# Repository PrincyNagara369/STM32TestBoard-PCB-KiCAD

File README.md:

# STM32TestBoard-PCB-KiCAD
Creating a PCB design for an STM32 test board using KiCad involves several steps. Below is a general outline of the process:

1. **Install KiCad:**
   If you haven't already, download and install the KiCad software from the official KiCad website (https://www.kicad-pcb.org/download/).

2. **Create a New Project:**
   - Open KiCad and create a new project for your STM32 test board.
   - Choose a suitable project name and location.

3. **Schematic Design:**
   - Start by creating a new schematic sheet in your project.
   - Add components to the schematic, including the STM32 microcontroller, power supply components, connectors, and any other peripherals you plan to include.
   - Connect the components by adding wires and creating appropriate nets.

4. **Component Libraries:**
   - Make sure you have the required component libraries for your components. KiCad comes with a set of default libraries, and you can also download additional libraries if needed.

5. **Footprint Assignment:**
   - Associate footprints with your schematic symbols. KiCad allows you to associate each component with a physical footprint used in the PCB layout.

6. **Schematic Annotation:**
   - Annotate the components on the schematic. KiCad will assign unique reference designators (e.g., U1, R1) to each component.

7. **Electrical Rule Check (ERC):**
   - Run an ERC to identify any potential connectivity or design rule errors in your schematic.

8. **Generate Netlist:**
   - Generate a netlist file from your schematic. The netlist is used to create the PCB layout.

9. **PCB Layout:**
   - Create a new PCB layout from the generated netlist.
   - Import footprints for your components or create custom footprints if necessary.
   - Place the components on the PCB layout, arranging them in a logical and organized manner.

10. **Connect Traces:**
    - Route the traces to connect the components according to your design.
    - Pay attention to signal integrity, power distribution, and ground plane.

11. **Design Rules Check (DRC):**
    - Run a DRC to ensure that your layout adheres to design rules such as minimum trace width, clearance, and other manufacturing specifications.

12. **Add Copper Pours and Planes:**
    - Create copper pours for power and ground connections.
    - Add ground and power planes if necessary for better signal integrity and noise reduction.

13. **3D Visualization:**
    - KiCad provides a 3D visualization tool that lets you preview your PCB in a realistic manner.

14. **Generate Gerber Files:**
    - Once you're satisfied with your PCB layout, generate the necessary Gerber files for manufacturing. These files include information about copper traces, solder mask, silkscreen, and more.

15. **Assembly Drawing:**
    - Create an assembly drawing that shows the component placements, reference designators, and other important details for assembling the PCB.

16. **Final Checks:**
    - Review your design thoroughly to ensure everything is correct and meets your requirements.

17. **Documentation:**
    - Create a documentation package that includes the schematic, PCB layout files, Gerber files, and any additional notes or instructions.

18. **Manufacturing:**
    - Send the Gerber files and other required documents to a PCB manufacturer for fabrication.

Remember that PCB design can be complex and requires attention to detail. It's also a good practice to consult the datasheets and reference manuals of your components, as well as any relevant PCB design guidelines from the microcontroller manufacturer. Additionally, there are many online resources, tutorials, and forums where you can find help and guidance during your KiCad PCB design journey.

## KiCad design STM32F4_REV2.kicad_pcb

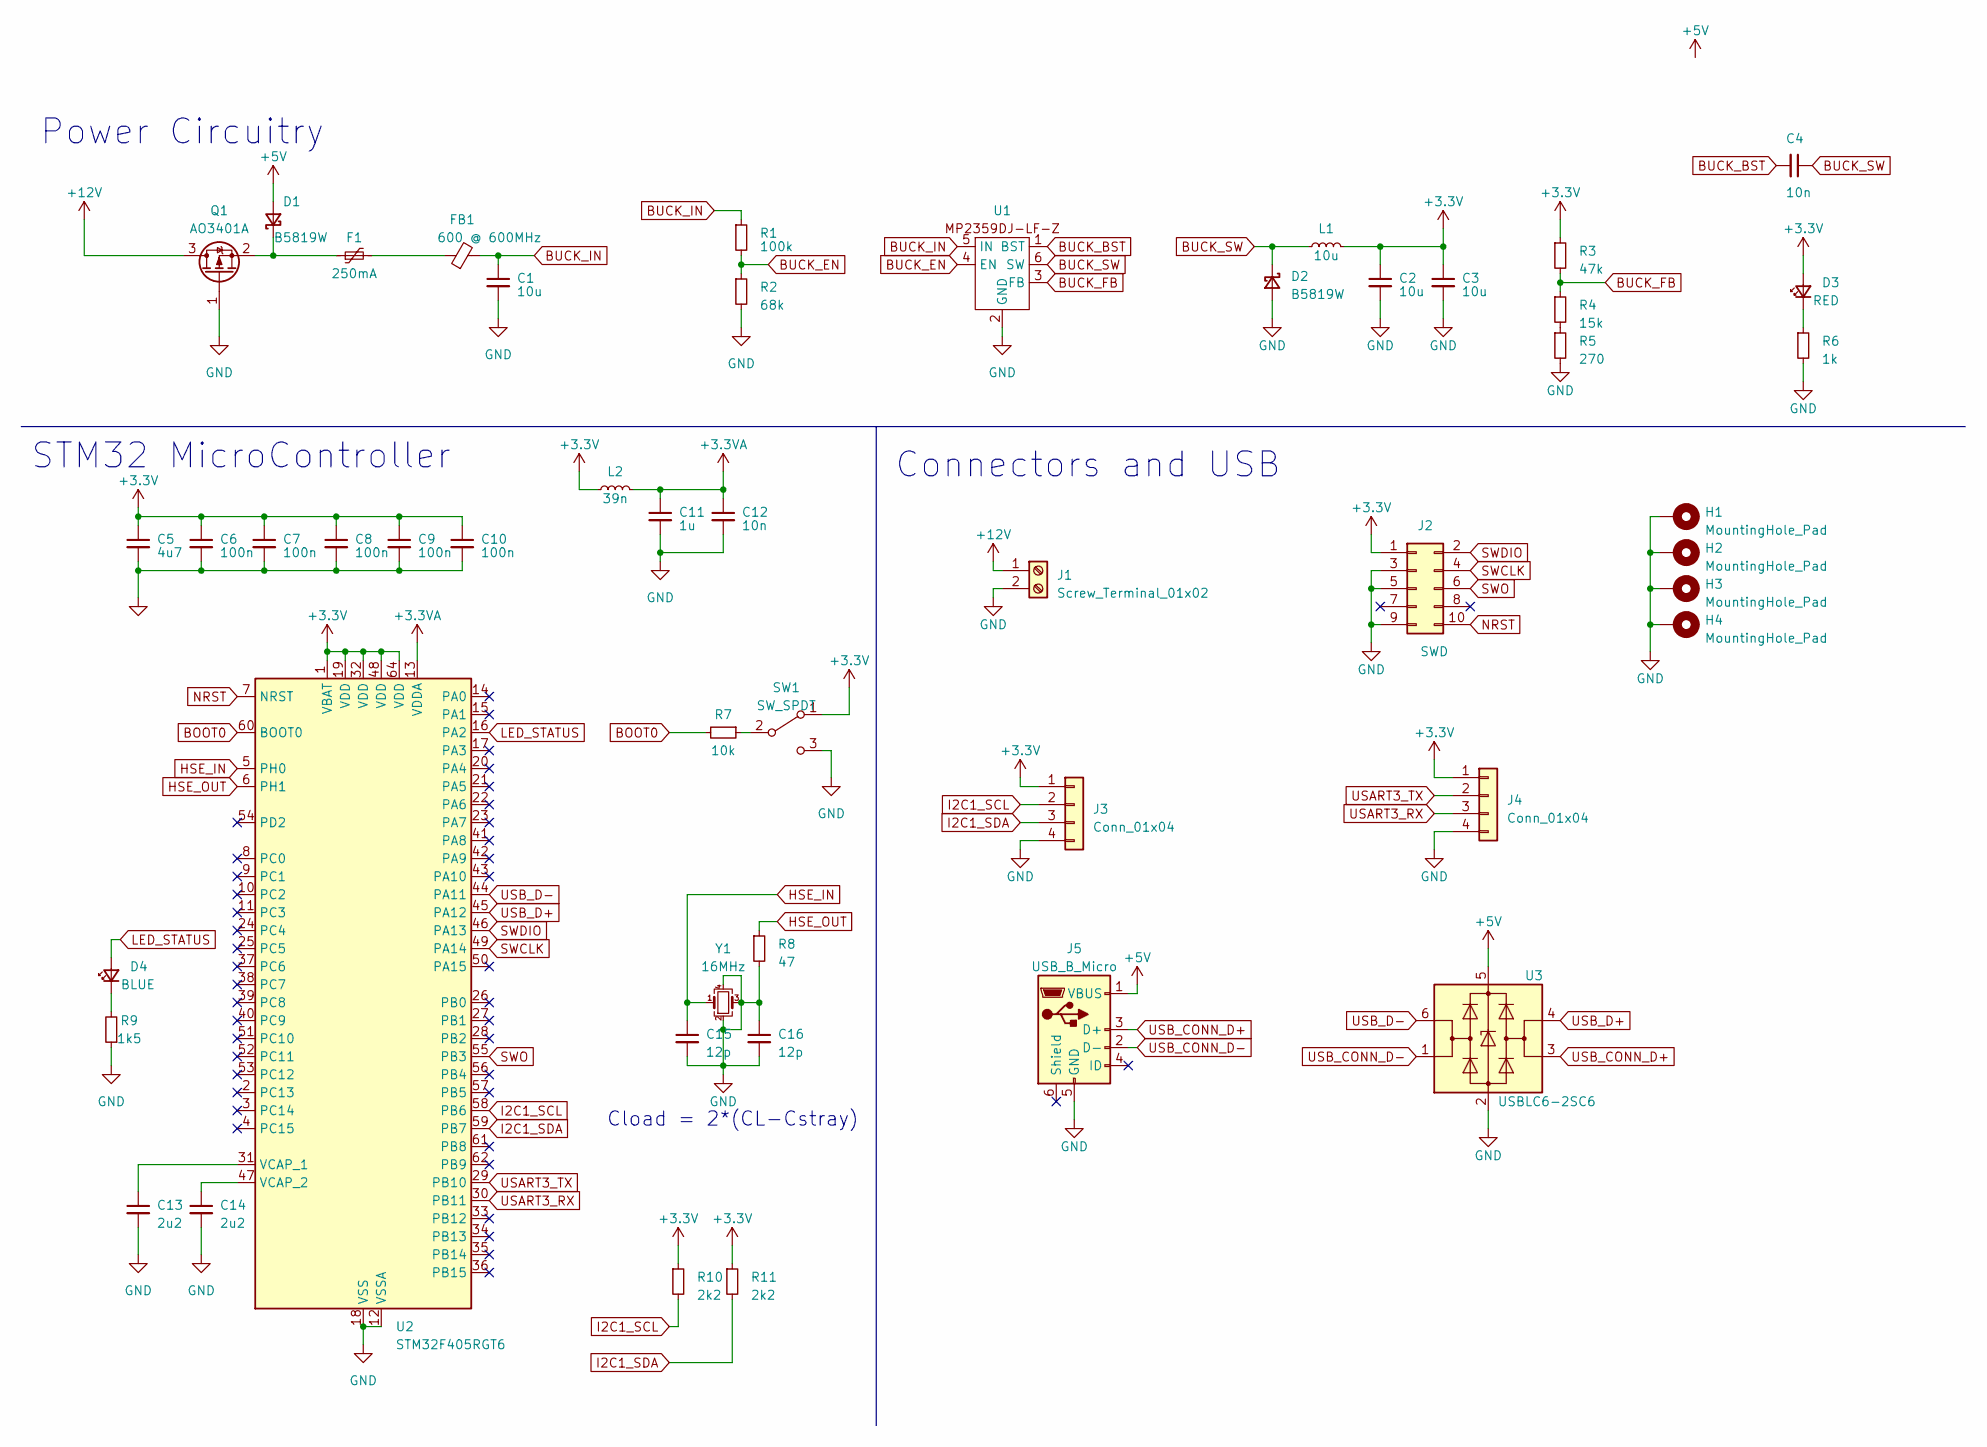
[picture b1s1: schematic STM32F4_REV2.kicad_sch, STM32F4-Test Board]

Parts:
C1, C2, C3: 10u; C_1206_3216Metric
C4: 10n; C_0603_1608Metric
C5: 4u7; C_0603_1608Metric
C6, C7, C8, C9, C10: 100n; C_0402_1005Metric
C11: 1u; C_0402_1005Metric
C12: 10n; C_0402_1005Metric
C13, C14: 2u2; C_0603_1608Metric
C15, C16: 12p; C_0402_1005Metric
D1, D2: B5819W; D_SOD-123
D3: RED; LED_0603_1608Metric
D4: BLUE; LED_0603_1608Metric
F1: 250mA; Fuse_1206_3216Metric
FB1: 600 @ 600MHz; L_0805_2012Metric
H1, H2, H3, H4: MountingHole_Pad; MountingHole_4.3mm_M4_Pad_Via
J1: Screw_Terminal_01x02; TerminalBlock_Phoenix_PT-1,5-2-3.5-H_1x02_P3.50mm_Horizontal
J2: SWD; PinHeader_2x05_P1.27mm_Vertical_SMD
J3, J4: Conn_01x04; Molex_PicoBlade_53048-0410_1x04_P1.25mm_Horizontal
J5: USB_B_Micro; USB_Micro-B_GCT_USB3076-30-A
L1: 10u; L_Sunlord_MWSA0518S
L2: 39n; L_0402_1005Metric
Q1: AO3401A; SOT-23
R1: 100k; R_0603_1608Metric
R2: 68k; R_0603_1608Metric
R3: 47k; R_0603_1608Metric
R4: 15k; R_0603_1608Metric
R5: 270; R_0603_1608Metric
R6: 1k; R_0603_1608Metric
R7: 10k; R_0402_1005Metric
R8: 47; R_0402_1005Metric
R9: 1k5; R_0603_1608Metric
R10, R11: 2k2; R_0402_1005Metric
SW1: SW_SPDT; SW_SPDT_PCM12
U1: SOT-23-6
U2: STM32F405RGT6; LQFP-64_10x10mm_P0.5mm
U3: USBLC6-2SC6; SOT-23-6
Y1: 16MHz; Crystal_SMD_3225-4Pin_3.2x2.5mm

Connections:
+3.3V: C2.1, C3.1, C5.1, C6.1, C7.1, C8.1, C9.1, C10.1, D3.2 (A), J2.1, J3.1, J4.1, L1.2, L2.1, R3.1, R10.1, R11.1, SW1.1 (A), U2.1 (VBAT), U2.19 (VDD), U2.32 (VDD), U2.48 (VDD), U2.64 (VDD)
+3.3VA: C11.1, C12.1, L2.2, U2.13 (VDDA)
+5V: D1.2 (A), J5.1 (VBUS), U3.5 (VBUS)
+12V: J1.1, Q1.3 (D)
BOOT0: R7.2, U2.60 (BOOT0)
BUCK_BST: C4.2, U1.1 (BST)
BUCK_EN: R1.2, R2.1, U1.4 (EN)
BUCK_FB: R3.2, R4.1, U1.3 (FB)
BUCK_IN: C1.1, FB1.2, R1.1, U1.5 (IN)
BUCK_SW: C4.1, D2.1 (K), L1.1, U1.6 (SW)
GND: C1.2, C2.2, C3.2, C5.2, C6.2, C7.2, C8.2, C9.2, C10.2, C11.2, C12.2, C13.2, C14.2, C15.2, C16.1, C16.2, D2.2 (A), H1.1, H2.1, H3.1, H4.1, J1.2, J2.3, J2.5, J2.9, J3.4, J4.4, J5.5 (GND), Q1.1 (G), R2.2, R5.2, R6.2, R8.2, R9.1, SW1.3 (C), U1.2 (GND), U2.12 (VSSA), U2.18 (VSS), U2.63 (VSS), U3.2 (GND), Y1.2, Y1.3, Y1.4
HSE_IN: C15.1, U2.5 (PH0), Y1.1
HSE_OUT: R8.1, U2.6 (PH1)
I2C1_SCL: J3.2, R10.2, U2.58 (PB6)
I2C1_SDA: J3.3, R11.2, U2.59 (PB7)
LED_STATUS: D4.2 (A), U2.16 (PA2)
NRST: J2.10, U2.7 (NRST)
unnamed: D1.1 (K), F1.1, Q1.2 (S)
unnamed: D3.1 (K), R6.1
unnamed: D4.1 (K), R9.2
unnamed: F1.2, FB1.1
unnamed: R4.2, R5.1
unnamed: R7.1, SW1.2 (B)
unnamed: C13.1, U2.31 (VCAP_1)
unnamed: C14.1, U2.47 (VCAP_2)
SWCLK: J2.4, U2.49 (PA14)
SWDIO: J2.2, U2.46 (PA13)
SWO: J2.6, U2.55 (PB3)
USART3_RX: J4.3, U2.30 (PB11)
USART3_TX: J4.2, U2.29 (PB10)
USB_CONN_D+: J5.3 (D+), U3.3 (I/O2)
USB_CONN_D-: J5.2 (D-), U3.1 (I/O1)
USB_D+: U2.45 (PA12), U3.4 (I/O2)
USB_D-: U2.44 (PA11), U3.6 (I/O1)

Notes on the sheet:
Connectors and USB
STM32 MicroController
Cload = 2*(CL-Cstray)
Power Circuitry

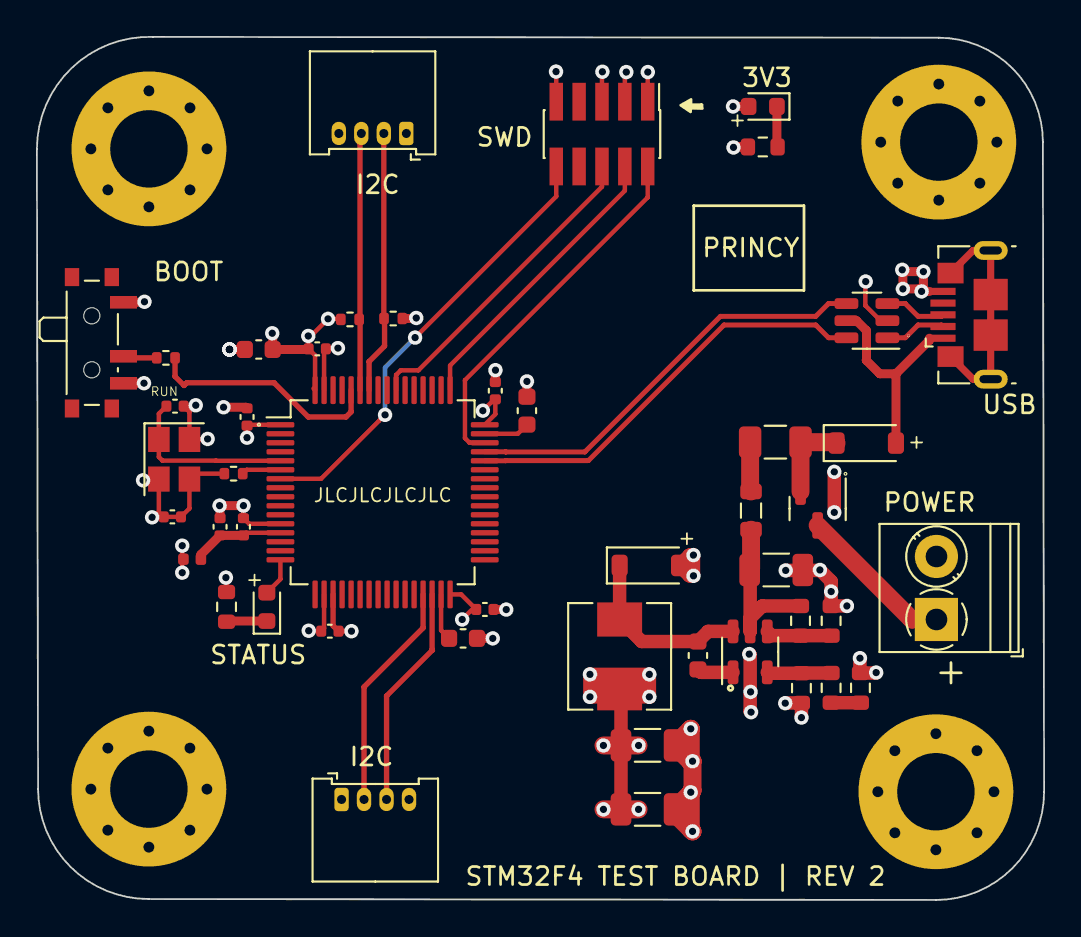
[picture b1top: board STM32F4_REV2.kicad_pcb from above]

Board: 4 copper layers, 56.0 x 47.9 mm, 50 parts (0 on the bottom side), 34 nets.

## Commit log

2023-08-27 README.md
